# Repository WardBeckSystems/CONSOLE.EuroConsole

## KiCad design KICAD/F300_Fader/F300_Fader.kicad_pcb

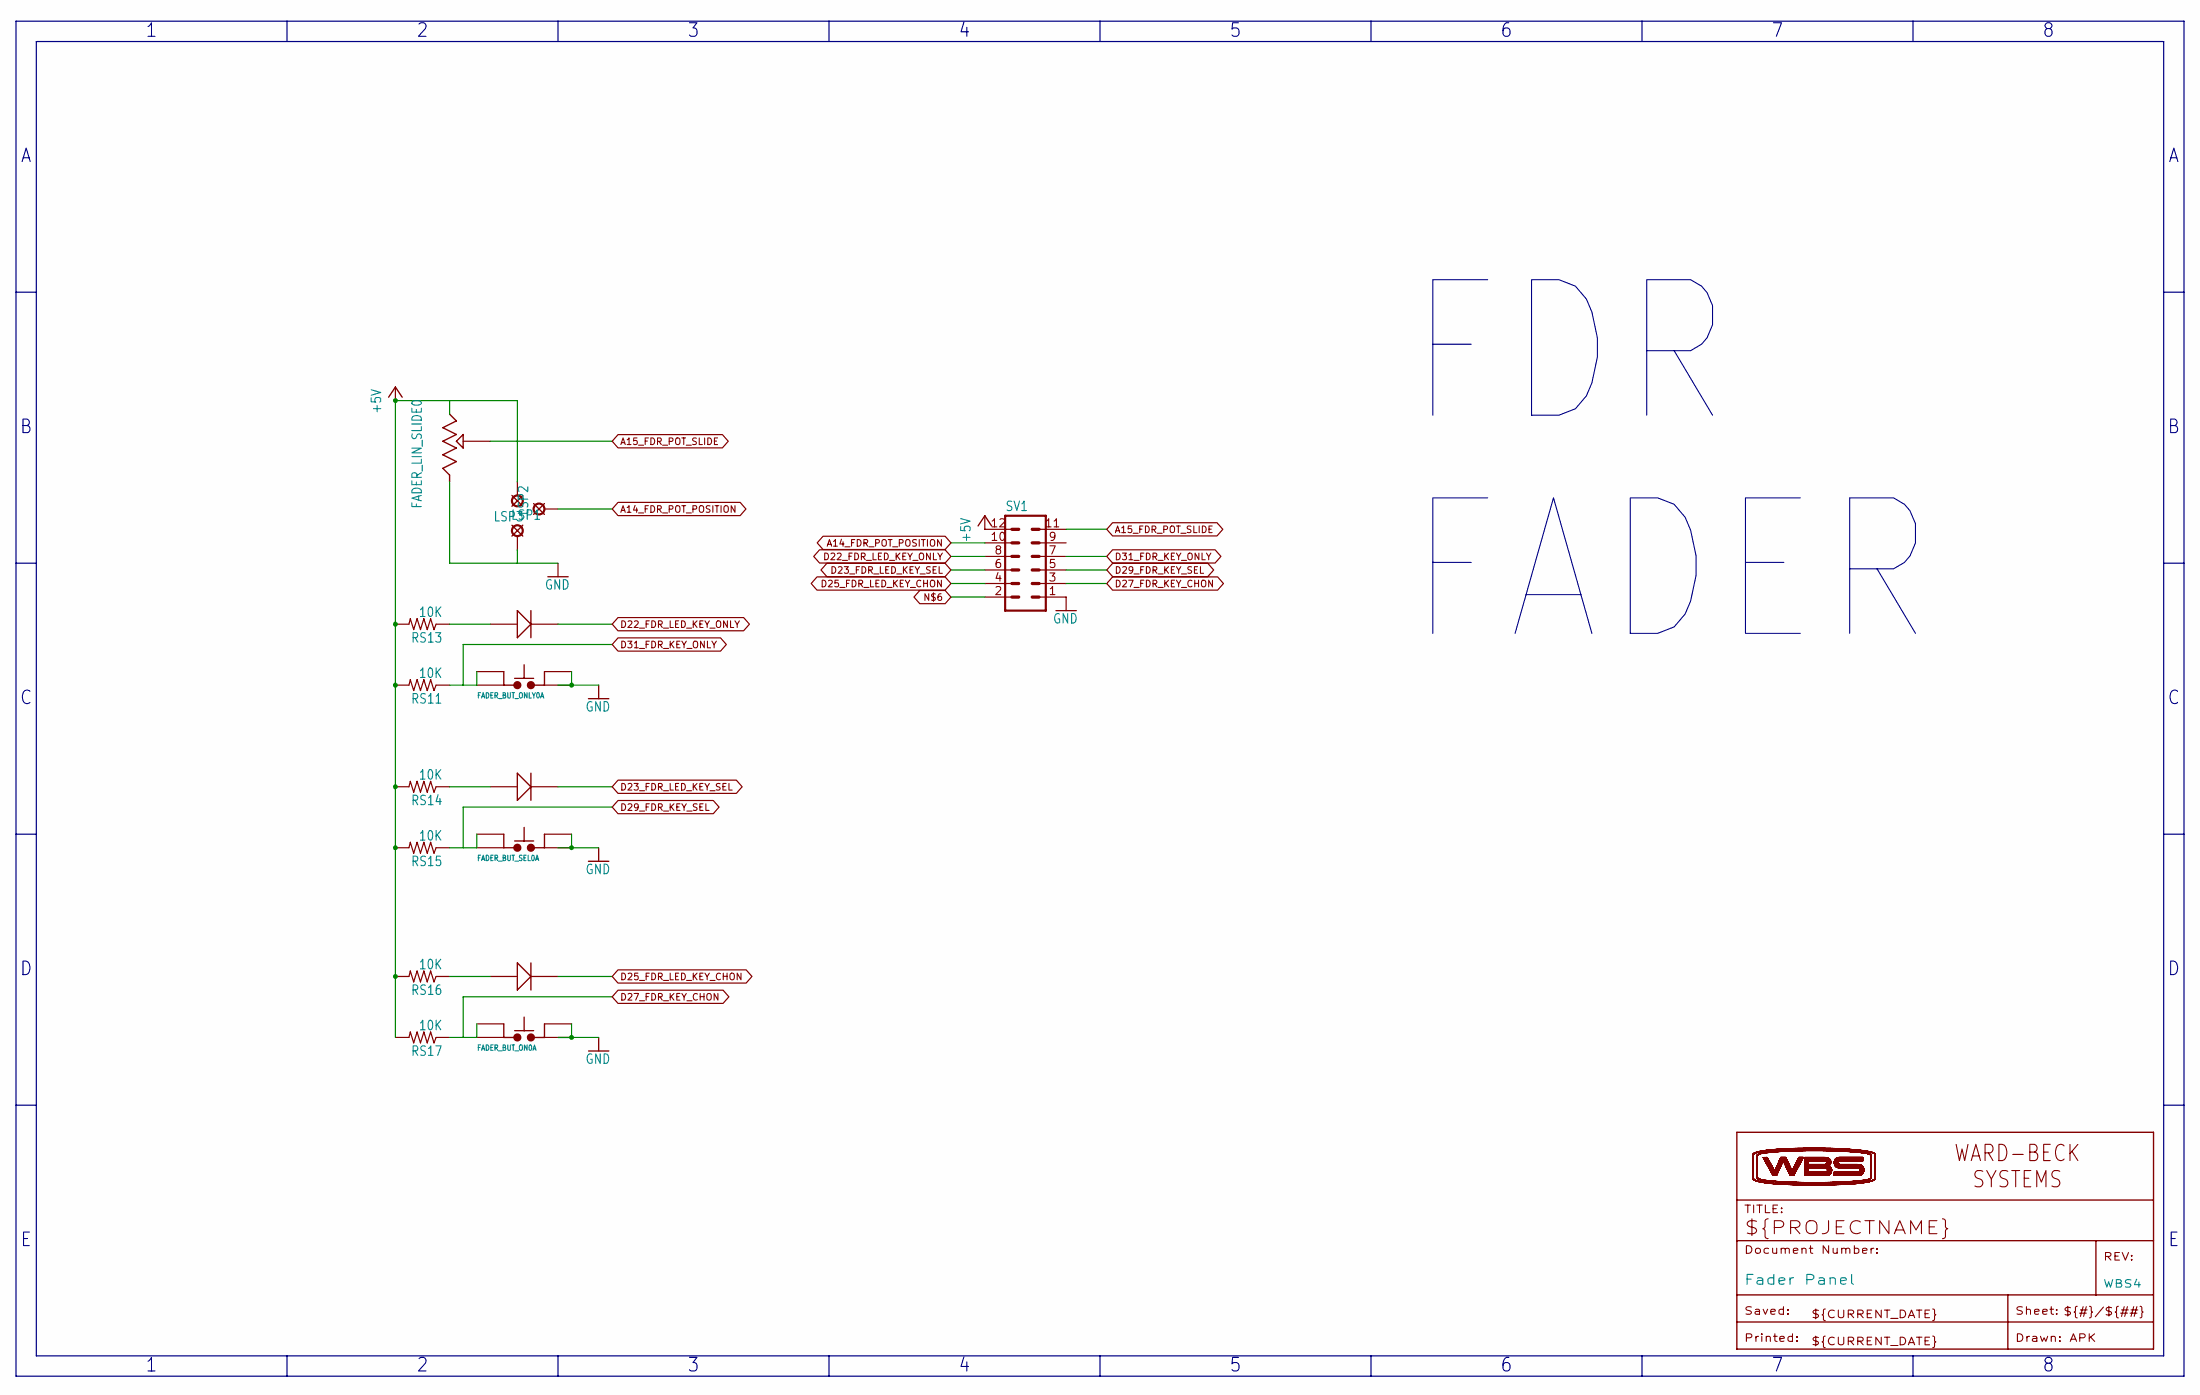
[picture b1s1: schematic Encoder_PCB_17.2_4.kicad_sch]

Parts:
FADER_BUT_ON0: SWITCH-POD-BUTTON_WITH_LED; SWITCH-PODBUTTON
FADER_BUT_ONLY0: SWITCH-POD-BUTTON_WITH_LED; SWITCH-PODBUTTON
FADER_BUT_SEL0: SWITCH-POD-BUTTON_WITH_LED; SWITCH-PODBUTTON
FADER_LIN_SLIDE0: BOURNS-PTA6043_SLIDEPOT
LSP1, LSP2, LSP3: MCS10B
RS11, RS13, RS14, RS15, RS16, RS17: 10K; M0805
SV1: MA06-2
WBS4: Fader Panel; WBS-FRAME_PCB

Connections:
+5V: FADER_LIN_SLIDE0.P$3 (CW), LSP3.MP, RS11.2, RS13.2, RS14.2, RS15.2, RS16.2, RS17.2, SV1.12
A14_FDR_POT_POSITION: LSP2.MP, SV1.10
A15_FDR_POT_SLIDE: FADER_LIN_SLIDE0.P$2 (WIPER), SV1.11
D22_FDR_LED_KEY_ONLY: FADER_BUT_ONLY0.LEDB, SV1.8
D23_FDR_LED_KEY_SEL: FADER_BUT_SEL0.LEDB, SV1.6
D25_FDR_LED_KEY_CHON: FADER_BUT_ON0.LEDB, SV1.4
D27_FDR_KEY_CHON: FADER_BUT_ON0.SW1A, FADER_BUT_ON0.SW2A, RS17.1, SV1.3
D29_FDR_KEY_SEL: FADER_BUT_SEL0.SW1A, FADER_BUT_SEL0.SW2A, RS15.1, SV1.5
D31_FDR_KEY_ONLY: FADER_BUT_ONLY0.SW1A, FADER_BUT_ONLY0.SW2A, RS11.1, SV1.7
GND: FADER_BUT_ON0.SW1B, FADER_BUT_ON0.SW2B, FADER_BUT_ONLY0.SW1B, FADER_BUT_ONLY0.SW2B, FADER_BUT_SEL0.SW1B, FADER_BUT_SEL0.SW2B, FADER_LIN_SLIDE0.P$1 (CCW), LSP1.MP, SV1.1
unnamed: FADER_BUT_ON0.LEDA, RS16.1
unnamed: FADER_BUT_SEL0.LEDA, RS14.1
unnamed: FADER_BUT_ONLY0.LEDA, RS13.1

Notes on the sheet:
FDR FADER

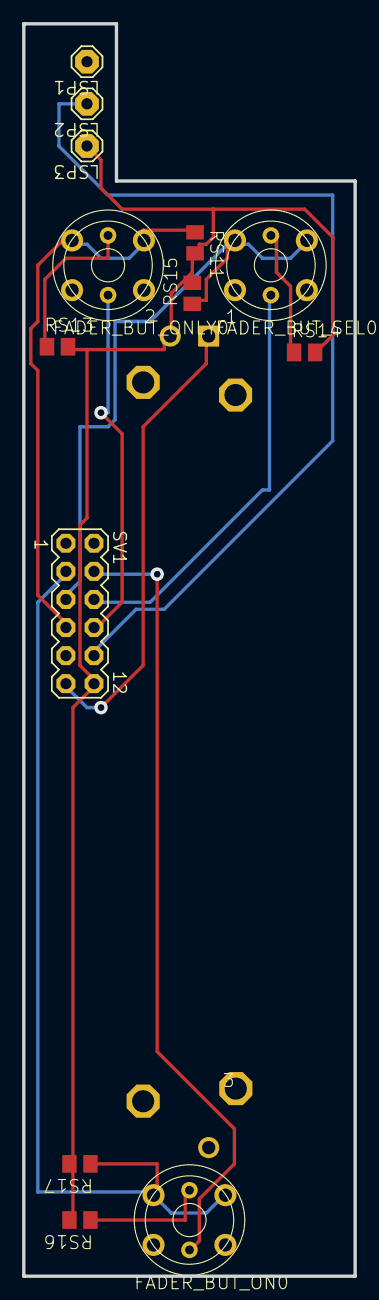
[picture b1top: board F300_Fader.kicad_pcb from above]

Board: 2 copper layers, 30.0 x 113.3 mm, 14 parts (0 on the bottom side), 13 nets.
